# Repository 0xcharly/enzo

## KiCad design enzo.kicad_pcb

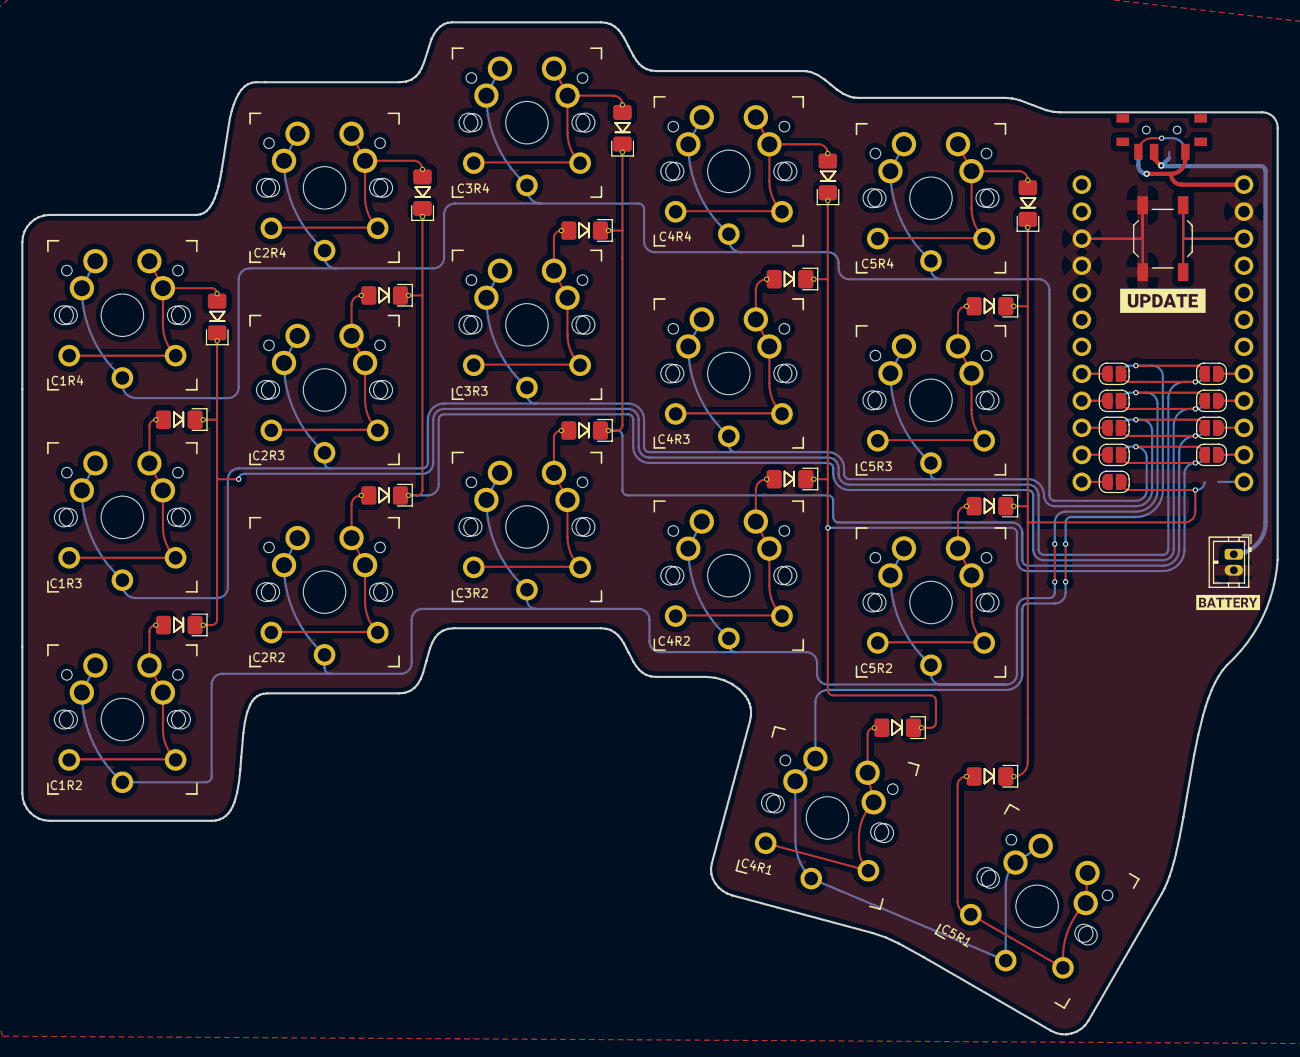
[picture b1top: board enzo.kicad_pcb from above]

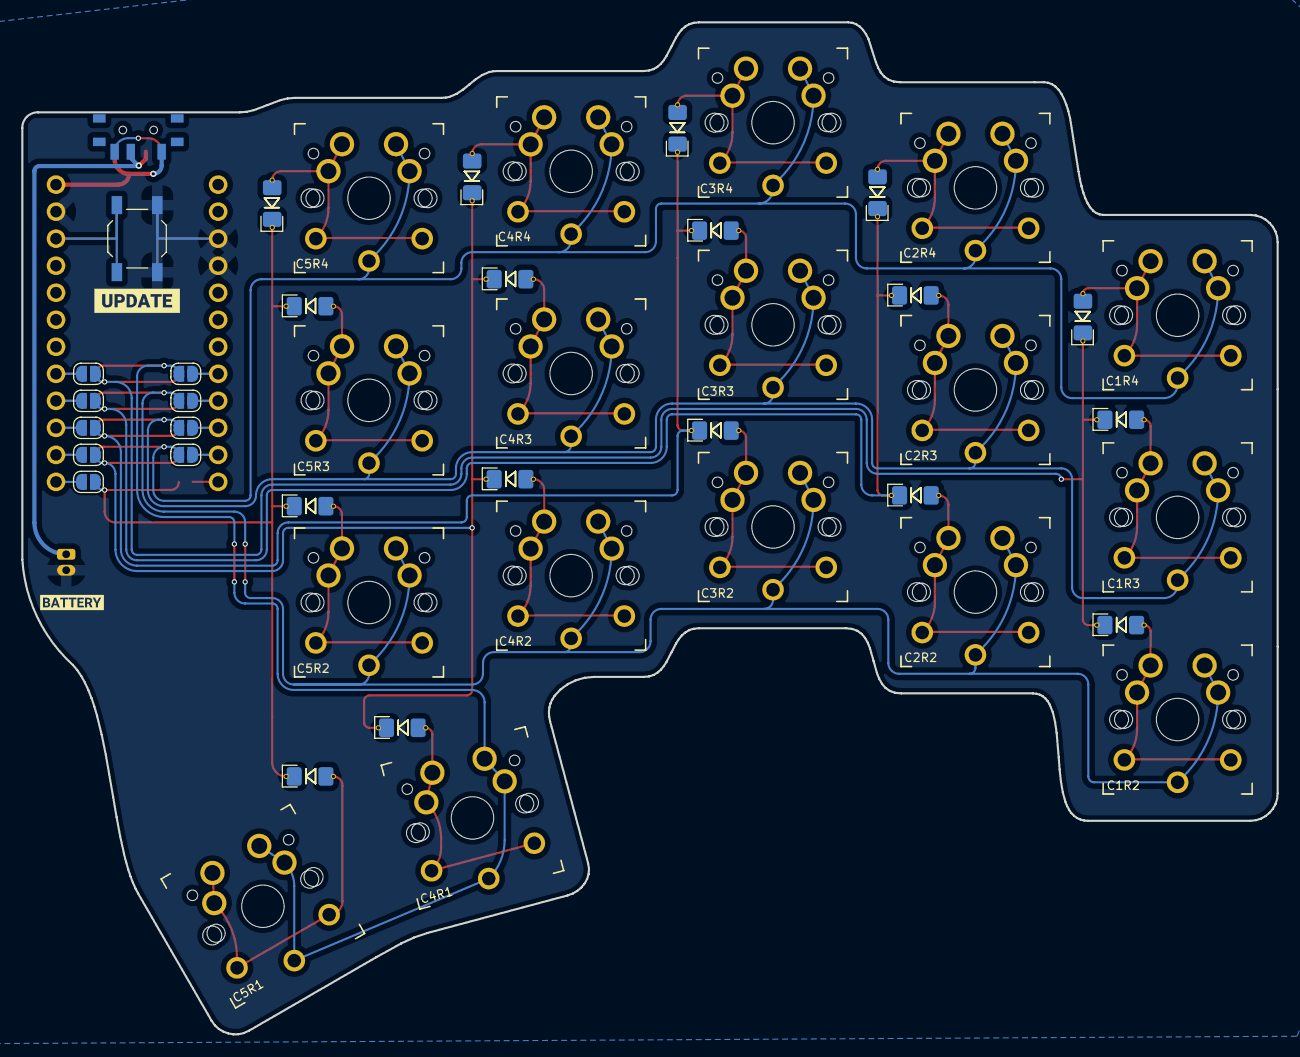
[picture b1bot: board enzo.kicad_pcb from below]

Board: 2 copper layers, 118.0 x 95.1 mm, 57 parts (11 on the bottom side), 34 nets.

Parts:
D3, D4, D5, D8, D9, D10, D13, D14, D15, D18, D19, D20, D24, D25, D26, D30, D33: D; D_1206_handsolder_reversible
JP_col_B1, JP_col_B2, JP_col_B3, JP_col_B4, JP_col_B5: SolderJumper-2_P1.3mm_Open_RoundedPad1.0x1.5mm
JP_col_F1, JP_col_F2, JP_col_F3, JP_col_F4, JP_col_F5: SolderJumper-2_P1.3mm_Open_RoundedPad1.0x1.5mm
JP_row_B1, JP_row_B2, JP_row_B3, JP_row_B4: SolderJumper-2_P1.3mm_Open_RoundedPad1.0x1.5mm
JP_row_F1, JP_row_F2, JP_row_F3, JP_row_F4: SolderJumper-2_P1.3mm_Open_RoundedPad1.0x1.5mm
PSW1: SW_DPDT_x2; Switch_MSK-12C01-07
SW1, SW2, SW3, SW4, SW5, SW6, SW7, SW8, SW9, SW10, SW11, SW12, SW13, SW14, SW15, SW16: SW_Push; SW_MX_choc
SW17: locked; SW_MX_choc
kibuzzard-61F01C84, kibuzzard-61F01C84#2: G***; kibuzzard-61F01C84
kibuzzard-628DFB5F, kibuzzard-628DFB5F#2: G***; kibuzzard-628DFB5F

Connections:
unnamed: D3.2 (A), SW1.2
unnamed: D4.2 (A), SW2.2
unnamed: D5.2 (A), SW3.2
unnamed: D8.2 (A), SW4.2
unnamed: D9.2 (A), SW5.2
unnamed: D10.2 (A), SW6.2
unnamed: D13.2 (A), SW7.2
unnamed: D14.2 (A), SW8.2
unnamed: D15.2 (A), SW9.2
unnamed: D18.2 (A), SW10.2
unnamed: D19.2 (A), SW11.2
unnamed: D20.2 (A), SW12.2
unnamed: D24.2 (A), SW13.2
unnamed: D25.2 (A), SW14.2
unnamed: D26.2 (A), SW15.2
unnamed: D30.2 (A), SW16.2
unnamed: D33.2 (A), SW17.2
col1_matrix: D3.1 (K), D4.1 (K), D5.1 (K), JP_col_B1.2, JP_col_F1.2
col1_mcu: JP_col_B1.1, JP_row_F1.2
col2_matrix: D8.1 (K), D9.1 (K), D10.1 (K), JP_col_B2.2, JP_col_F2.2
col2_mcu: JP_col_B2.1, JP_row_F2.2
col3_matrix: D13.1 (K), D14.1 (K), D15.1 (K), JP_col_B3.2, JP_col_F3.2
col3_mcu: JP_col_B3.1, JP_row_F3.2
col4_matrix: D18.1 (K), D19.1 (K), D20.1 (K), D30.1 (K), JP_col_B4.2, JP_col_F4.2
col4_mcu: JP_col_B4.1, JP_row_F4.2
col5_matrix: D24.1 (K), D25.1 (K), D26.1 (K), D33.1 (K), JP_col_B5.2, JP_col_F5.2
row1_matrix: JP_row_B1.1, JP_row_F1.1, SW16.1, SW17.1
row1_mcu: JP_col_F1.1, JP_row_B1.2
row2_matrix: JP_row_B2.1, JP_row_F2.1, SW3.1, SW6.1, SW9.1, SW12.1, SW15.1
row2_mcu: JP_col_F2.1, JP_row_B2.2
row3_matrix: JP_row_B3.1, JP_row_F3.1, SW2.1, SW5.1, SW8.1, SW11.1, SW14.1
row3_mcu: JP_col_F3.1, JP_row_B3.2
row4_matrix: JP_row_B4.1, JP_row_F4.1, SW1.1, SW4.1, SW7.1, SW10.1, SW13.1
row4_mcu: JP_col_F4.1, JP_row_B4.2

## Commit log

2022-08-12 Add reset button footprint
2022-08-12 Add traces for the reset button
2022-08-12 Minor trace tweaks/cleanup
2022-08-12 Use the proper ground layer
2022-08-12 Fix schematics
2022-08-12 Fix design
2022-08-12 Save before updating from schematics
2022-08-12 PCB: fix mcu pins definition
2022-08-12 Another take at the jumper design, starting from the schematics
2022-08-12 Finish jumpers schematics
2022-08-12 Finally cleaned up jumper situation
2022-08-12 Cleaned up warnings in schematics
2022-08-12 Fix traces
2022-08-13 Add .gitignore
